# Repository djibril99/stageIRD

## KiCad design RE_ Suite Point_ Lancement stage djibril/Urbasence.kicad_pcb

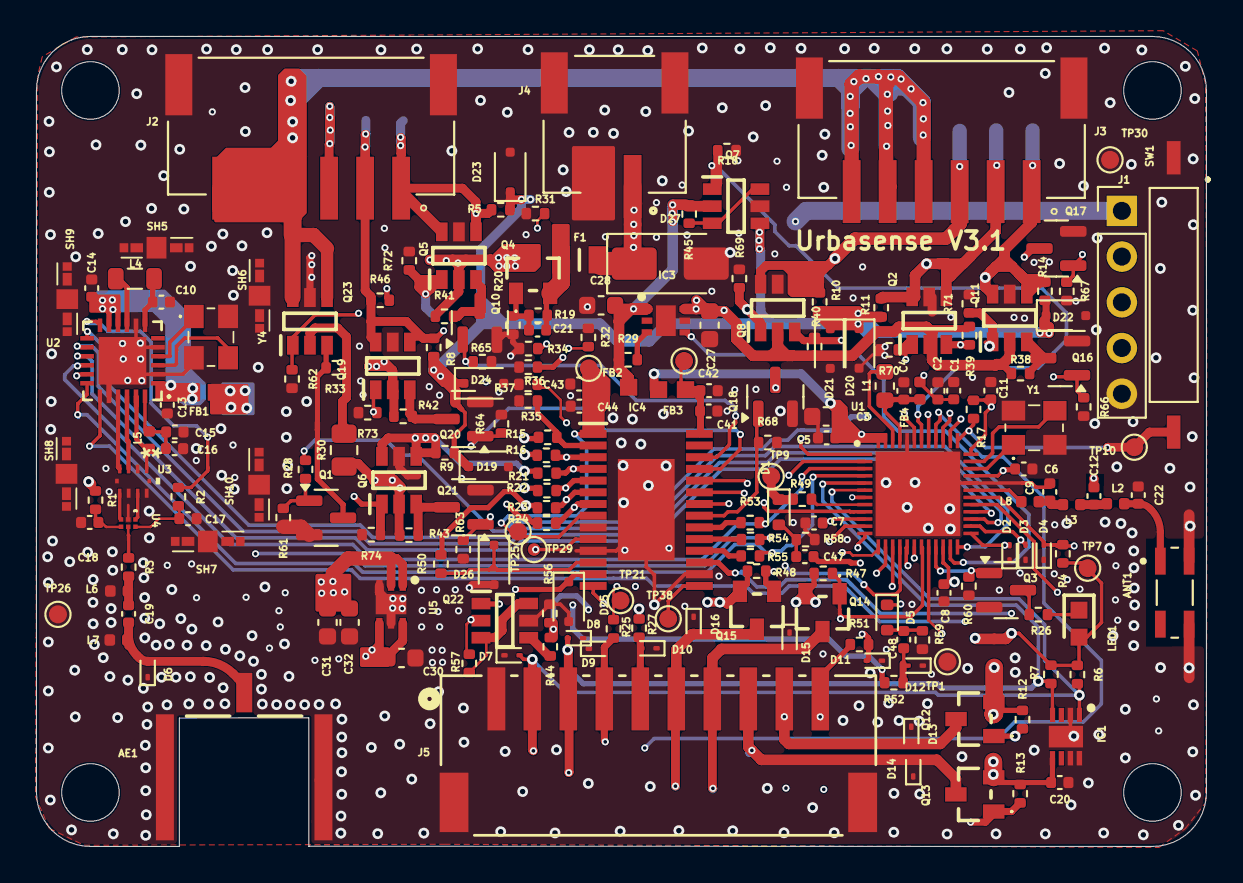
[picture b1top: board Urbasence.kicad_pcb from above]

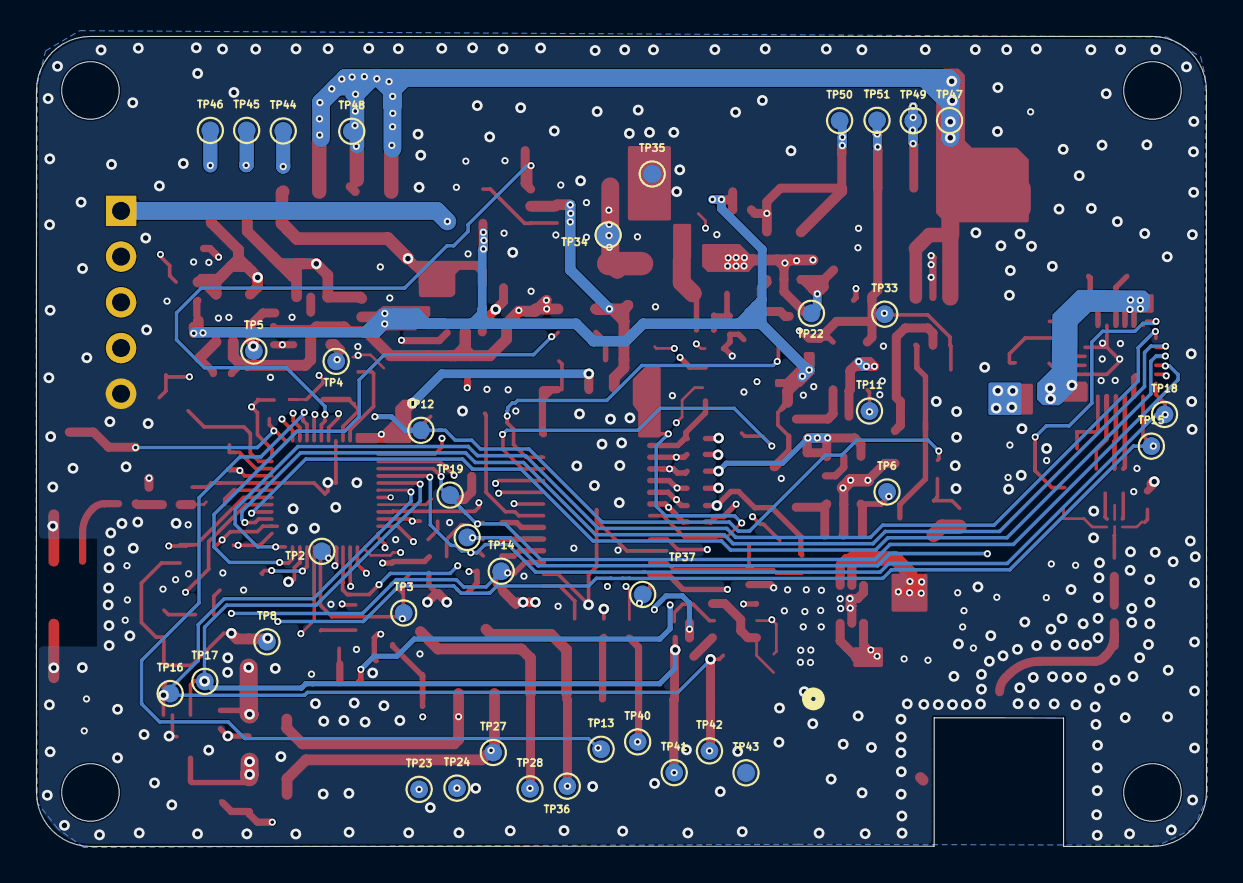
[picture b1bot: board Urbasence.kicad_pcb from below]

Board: 4 copper layers, 65.0 x 45.0 mm, 246 parts (38 on the bottom side), 124 nets.

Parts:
AE1: 60312202114307
ANT1: 2450AT42E0100E; XDCR_2450AT42E0100E
C1, C4, C41, C44: 2.2uF; C_0402_1005Metric
C2, C6: 10nF; C_0402_1005Metric
C3, C28, C31, C32: 10uF; C_0603_1608Metric
C5, C7, C8, C11, C14, C20, C42, C43: 100nF; C_0402_1005Metric
C9: 1.5pF; C_0402_1005Metric
C10: 470nF; C_0402_1005Metric
C12: 2pF; C_0402_1005Metric
C13, C21, C47, C48: 1uF; C_0402_1005Metric
C15: 47nF; C_0402_1005Metric
C16: 47pF; C_0402_1005Metric
C17, C18: 1nF; C_0402_1005Metric
C19: 4.7pF; C_0402_1005Metric
C22: 0.3pF; C_0402_1005Metric
C27: 1uF; C_0603_1608Metric
C30: 4.7uF/25V; C_0603_1608Metric
D1, D5: 1N4148WT; D_SOD-523
D2, D3, D4, D7, D8, D9, D10, D11, D12, D13, D14, D15, D16: ESD9B3.3ST5G; D_SOD-923
D6: ESD9B5.0ST5G; D_SOD-923
D19, D20, D21, D22, D23, D24, D25, D26: MM3Z5V1T1G; D_SOD-323F
D27: SMAJ9.0A; D_SMA
F1: MF-PSHT050KX-2; FUSE 500mA 0ZCK0050FF2E
FB1, FB2, FB3: 3A; FERIT_BLM18_0603_MUR
FB4: 3A; L_0402_1005Metric
H1, H2, H3, H4: MountingHole_Pad; MountingHole_3.2mm_M3
IC1: STS35-DIS; STS35-SON50P250X250X100-9N-D
IC3: TPS7A2650DRVR; TPS7A26-SON65P200X200X80-7N
IC4: LMP90100MHX_NOPB; LMP90100-SOP65P640X110-29N
J1: Flashing; PinHeader_1x05_P2.54mm_Vertical
J2, J3: Conn_01x06; JST_S6B-PH-SM4-TB_LF__SN_
J4: Conn_01x02; JST_S2B-PH-SM4-TB_LF__SN_
J5: Conn_01x10; CONN_S10B-PH-SM4-TBLFSN_JST
L1: 4.7uH; L_0603_1608Metric
L2, L3: 3.5nH; L_0402_1005Metric
L4: 15uH; L_0805_2012Metric
L5: 47nH; L_0402_1005Metric
L6, L7: 150nH; L_0402_1005Metric
L8: 2.7nH; L_0402_1005Metric
LED1: LED_0603
Q1, Q3, Q10, Q16, Q17, Q18, Q20, Q21: 2N7002; SOT-23
Q2, Q5, Q6, Q7, Q8, Q11, Q19, Q22, Q23: DMC2053-SOP95P280X100-6N
Q4, Q12, Q13, Q14, Q15: SSM3J372R,LF; SSM3J372RLF
R1, R2: 100R; R_0402_1005Metric
R3, R28, R49, R53, R54, R55: 0; R_0402_1005Metric
R4, R12, R13, R17, R18, R19, R29, R47, R48, R58, R59, R60, R61, R62, R63, R64, R65, R66, R67, R68, R69, R70, R71, R72, R73, R74: 10k; R_0402_1005Metric
R5, R8, R9, R10, R11, R14: 10k/0.5%; R_0402_1005Metric
R6, R7: 4.7k; R_0402_1005Metric
R15, R16, R21, R22, R23, R24: 1k/0.5%; R_0402_1005Metric
R20: 20k; R_0402_1005Metric
R25, R27: 22; R_0402_1005Metric
R26: 470R; R_0402_1005Metric
R30: 0; R_0805_2012Metric
R31, R32, R34, R35, R36, R37: 47k; R_0402_1005Metric
R33, R38, R39, R40, R41, R42, R43, R45: 100k; R_0402_1005Metric
R44: 27k; R_0402_1005Metric
R46, R50, R51, R52: 1k; R_0402_1005Metric
R56: 10K; R_0402_1005Metric
R57: 100K; R_0402_1005Metric
SH5, SH6, SH7, SH8, SH9, SH10: S0951-46R; S095146R
SW1: CT10-1530-G1
TP1, TP2, TP3, TP4, TP5, TP6, TP7, TP8, TP9, TP10, TP11, TP12, TP13, TP14, TP15, TP16, TP17, TP18, TP19, TP20, TP21, TP22, TP23, TP24, TP25, TP26, TP27, TP28, TP29, TP30, TP31, TP32, TP33, TP34, TP35, TP36, TP37, TP38, TP40, TP41, TP42, TP43, TP44, TP45, TP46, TP47, TP48, TP49, TP50, TP51: TestPoint; TestPoint_Pad_D1.0mm
U1: NRF54l15-QFAA; nRF52840-QFAA-F-R7
U2: SX1262IMLTRT
U3: 0900FM15K0039E; 0900FM15D0039E_JOT
U4: BGS12WN6E6327XTSA1; PG-TSNP-6-10_INF
U5: TLV76733DRVT; SON65P200X200X80-7N
Y1, Y4: 32MHz; ECS2501033BCKMTR

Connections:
3V3: C3.2, C5.2, C7.2, C8.2, C11.2, C20.2, C31.2, C32.2, FB1.2, FB3.1, IC1.5 (VDD), J1.1, LED1.2, Q12.2 (S), Q13.2 (S), Q14.2 (S), Q15.2 (S), R4.1, R6.1, R7.1, R12.1, R13.1, R17.1, R47.1, R48.1, TP7.1, TP8.1, U1.10 (VDD), U1.22 (VDD), U1.36 (VDD), U1.47 (Vdd), U1.48 (Vdd), U5.1 (OUT), U5.2 (SNS)
5V: C28.2, FB2.2, IC3.1 (OUT), Q7.2 (S2), R29.1, R45.1
/LMP90100/COM: J2.4, J2.5, J2.6, J3.4, J3.5, J3.6, Q23.4 (D2), Q23.6 (D2), TP47.1, TP48.1
/LMP90100/WM1/EV1: J2.1, Q5.4 (D2), Q5.6 (D2), R5.2, R15.1, R52.1, TP50.1
/LMP90100/WM2/EV2: J2.2, Q19.4 (D2), Q19.6 (D2), R8.2, R16.1, R46.1, TP51.1
/LMP90100/WM3/EV3: J2.3, Q6.4 (D2), Q6.6 (D2), R9.2, R21.1, TP49.1
/LMP90100/WM4/EV4: J3.1, Q11.4 (D2), Q11.6 (D2), R14.2, R22.1, TP46.1
/LMP90100/WM5/EV5: J3.2, Q2.4 (D2), Q2.6 (D2), R11.2, R23.1, R50.1, TP45.1
/LMP90100/WM6/EV6: J3.3, Q8.4 (D2), Q8.6 (D2), R10.2, R24.1, TP44.1
/nRF54L15/TOR/Counter1: D1.1 (K), R49.2, TP9.1
BAT_CHECK: IC4.10 (VIN6/VREFP2), R44.2, R56.1, TP29.1
BUSY: U1.27 (P0.02), U2.14 (BUSY)
CLK: R55.2, TP18.1, U1.4 (P1.03/NFC2), U2.18 (SCK)
CS1: TP15.1, U1.38 (P1.10), U2.19 (NSS)
CS2: IC4.17 (CSB), TP14.1, U1.39 (P1.11/AIN4/CK)
Control_COM: Q23.1 (G1), R62.1, TP33.1, U1.11 (P2.00)
Control_COM_Hi: R28.2, TP12.1, U1.41 (P1.13/AIN6)
Control_WM1: Q5.1 (G1), R72.1, TP22.1, U1.12 (P2.01/CK)
Control_WM1_Hi: IC4.26 (D5), Q10.1 (G), R65.1
Control_WM2: Q19.1 (G1), R73.1, TP11.1, U1.13 (P2.02)
Control_WM2_Hi: IC4.25 (D4), Q20.1 (G), R64.1
Control_WM3: Q6.1 (G1), R74.1, TP6.1, U1.14 (P2.03)
Control_WM3_Hi: IC4.24 (D3), Q21.1 (G), R63.1
Control_WM4: Q11.1 (G1), R71.1, TP5.1, U1.15 (P2.04)
Control_WM4_Hi: IC4.23 (D2), Q16.1 (G), R66.1
Control_WM5: Q2.1 (G1), R70.1, TP4.1, U1.16 (P2.05)
Control_WM5_Hi: IC4.22 (D1), Q17.1 (G), R67.1
Control_WM6: Q8.1 (G1), R69.1, U1.17 (P2.06/CK)
Control_WM6_Hi: IC4.21 (D0), Q18.1 (G), R68.1
Controled_5V: Q7.1 (G1), R18.1, U1.42 (P1.14/AIN7)
DIO1: U1.24 (P0.01), U2.13 (DIO1)
EN_5V: IC3.4 (EN), U1.23 (P0.00)
EN_BAT_CHECK: Q22.1 (G1), U1.9 (P1.08/EXTREF/CLK16M/ck)
ETX1: Q15.1 (G), R48.2, TP2.1, U1.18 (P2.07/SWO)
ETX2: Q14.1 (G), R47.2, TP3.1, U1.19 (P2.08)
ETX3: Q13.1 (G), R13.2, U1.20 (P2.09)
ETX4: Q12.1 (G), R12.2, U1.29 (P0.04CK)
GND: AE1.2, AE1.3, ANT1.3, ANT1.4, C1.1, C2.1, C3.1, C4.1, C5.1, C6.1, C7.1, C8.1, C9.1, C10.1, C11.1, C12.1, C13.1, C14.1, C15.2, C16.2, C17.2, C18.2, C20.1, C22.1, C27.1, C28.1, C30.1, C31.1, C32.1, C41.1, C42.1, C43.1, C44.1, D2.1 (A1), D3.1 (A1), D4.1 (A1), D6.1 (A1), D7.1 (A1), D8.1 (A1), D9.1 (A1), D10.1 (A1), D11.1 (A1), D12.1 (A1), D13.1 (A1), D14.1 (A1), D15.1 (A1), D16.1 (A1), D19.2 (A), D20.2 (A), D21.2 (A), D22.2 (A), D23.2 (A), D24.2 (A), D25.2 (A), D26.2 (A), D27.2 (A2), IC1.2 (ADDR), IC1.7 (R), IC1.8 (VSS), IC1.9 (GND), IC3.5 (GND), IC3.7 (EP), IC4.9 (VREFN1), IC4.11 (VIN7/VREFN2), IC4.16 (GND), IC4.29 (EP), J1.5, J2.S1, J2.S2, J3.S1, J3.S2, J4.2, J4.S2, J4.g, J5.1, J5.11, J5.12, L6.1, L7.1, Q1.2 (S), Q2.5 (S1), Q3.2 (S), Q5.5 (S1), Q6.5 (S1), Q7.5 (S1), Q8.5 (S1), Q10.2 (S), Q11.5 (S1), Q16.2 (S), Q17.2 (S), Q18.2 (S), Q19.5 (S1), Q20.2 (S), Q21.2 (S), Q22.5 (S1), Q23.5 (S1), R18.2, R20.2, R31.1, R32.1, R34.2, R35.1, R36.1, R37.1, R56.2, R58.2, R59.2, R60.2, R61.2, R62.2, R63.2, R64.2, R65.2, R66.2, R67.2, R68.2, R69.2, R70.2, R71.2, R72.2, R73.2, R74.2, SH5.1, SH5.2, SH5.3, SH5.4, SH5.5, SH6.1, SH6.2, SH6.3, SH6.4, SH6.5, SH7.1, SH7.2, SH7.3, SH7.4, SH7.5, SH8.1, SH8.2, SH8.3, SH8.4, SH8.5, SH9.1, SH9.2, SH9.3, SH9.4, SH9.5, SH10.1, SH10.2, SH10.3, SH10.4, SH10.5, SW1.1, TP1.1, TP26.1, TP30.1, TP35.1, TP43.1, U1.32 (Vss_PA), U1.44 (Vss), U1.49 (Vss), U2.2 (GND), U2.5 (GND), U2.8 (GND), U2.20 (GND), U2.25 (GND), U3.2 (GND), U3.5 (GND), U3.7 (GND), U3.9 (GND), U3.10 (GND), U4.2 (GND), U5.3 (GND_1), U5.5 (GND_2), U5.7 (EP), Y1.2, Y1.4, Y4.2, Y4.4
I2C_SCK: D8.2 (A2), IC1.4 (SCL), J5.3, R7.2, TP17.1, TP41.1, U1.5 (P1.04/AIN0)
I2C_SDA: D7.2 (A2), IC1.1 (SDA), J5.2, R6.2, TP16.1, TP42.1, U1.6 (P1.05/AIN1)
L_RESET: U1.28 (P0.03CK), U2.15 (NRESET)
MISO: R53.2, TP19.1, U1.3 (P1.02/NFC1), U2.16 (MISO)
MOSI: R54.2, TP20.1, U1.2 (P1.01/XL2), U2.17 (MOSI)
unnamed: ANT1.1, C22.2, L2.2
unnamed: C9.2, L3.1, L8.2
unnamed: C12.2, L2.1, L3.2
unnamed: C19.1, L6.2, R3.2
unnamed: C47.1, D1.2 (A), R58.1
unnamed: C48.1, D5.2 (A), R59.1
unnamed: AE1.1, C19.2, D6.2 (A2), L7.2
unnamed: D9.2 (A2), J5.4, R25.1, TP40.1
unnamed: D10.2 (A2), J5.5, R27.1
unnamed: C47.2, D11.2 (A2), R51.2
unnamed: C48.2, D12.2 (A2), R52.2
unnamed: D13.2 (A2), J5.9, Q12.3 (D), TP24.1
unnamed: D14.2 (A2), J5.8, Q13.3 (D), TP27.1
unnamed: D15.2 (A2), J5.7, Q14.3 (D), TP28.1
unnamed: D16.2 (A2), J5.6, Q15.3 (D), TP36.1
unnamed: D19.1 (K), D20.1 (K), D21.1 (K), D22.1 (K), D23.1 (K), D24.1 (K), Q7.4 (D2), R5.1, R8.1, R9.1, R10.1, R11.1, R14.1
unnamed: D25.1 (K), IC4.13 (IB1), R46.2
unnamed: D26.1 (K), IC4.12 (IB2), R50.2
unnamed: D27.1 (A1), F1.1, J4.1, TP34.1
unnamed: IC3.3 (PG), R29.2
unnamed: IC4.18 (SCLK), R55.1
unnamed: IC4.19 (SDI), R54.1
unnamed: IC4.20 (SDO/DRDYB), R53.1
unnamed: C43.2, C44.2, FB2.1, IC4.1 (VA), IC4.8 (VREFP1), TP25.1, TP32.1
unnamed: IC4.2 (VIN0), R15.2, R35.2
unnamed: IC4.3 (VIN1), R16.2, R37.2
unnamed: IC4.4 (VIN2), R21.2, R36.2
unnamed: IC4.5 (VIN3), R22.2, R34.1
unnamed: IC4.6 (VIN4), R23.2, R32.2
unnamed: IC4.7 (VIN5), R24.2, R31.2
unnamed: C41.2, C42.2, FB3.2, IC4.28 (VIO), TP31.1
unnamed: IC4.15 (XIN/CLK), TP38.1
unnamed: IC4.14 (XOUT), TP37.1
unnamed: J5.10, R51.1, TP23.1
unnamed: LED1.1, R26.1
unnamed: Q1.3 (D), Q23.3 (G2), R33.2
unnamed: Q1.1 (G), R28.1, R61.1
unnamed: Q3.3 (D), R26.2
unnamed: Q3.1 (G), R60.1, U1.21 (P2.10)
unnamed: C21.1, Q4.1 (G), R19.2, R20.1
unnamed: C21.2, F1.2, Q4.2 (S), R19.1
unnamed: Q7.3 (G2), Q7.6 (D2), R45.2
unnamed: Q5.3 (G2), Q10.3 (D), R41.2
unnamed: Q11.3 (G2), Q16.3 (D), R38.2
unnamed: Q2.3 (G2), Q17.3 (D), R39.2
unnamed: Q8.3 (G2), Q18.3 (D), R40.2
unnamed: Q19.3 (G2), Q20.3 (D), R42.2
unnamed: Q6.3 (G2), Q21.3 (D), R43.2
unnamed: Q22.3 (G2), Q22.6 (D2), R57.1
unnamed: Q22.4 (D2), R44.1
unnamed: Q23.2 (S2), R30.2, R33.1
unnamed: L8.1, U1.31 (Ant)
unnamed: L1.2, U1.46 (DCC)
unnamed: C1.2, C2.2, C6.2, FB4.2, U1.33 (DECRF), U1.43 (DECA)
unnamed: C4.2, FB4.1, L1.1, U1.45 (DECD)
unnamed: U1.34 (XC1), Y1.1
unnamed: U1.35 (XC2), Y1.3
unnamed: R49.1, U1.8 (P1.07/AIN3)
unnamed: R17.2, SW1.2, TP10.1, U1.37 (P1.09)
unnamed: L4.2, U2.9 (DCC_SW)
unnamed: R2.2, U2.12 (DIO2)
unnamed: U2.22 (RFI_N), U3.3 (RFI_N)
unnamed: U2.21 (RFI_P), U3.4 (RFI_P)
unnamed: L5.2, U2.23 (RFO), U3.1 (RFO)
unnamed: C10.2, L4.1, U2.7 (VREG)
unnamed: C15.1, C16.1, L5.1, U2.24 (VR_PA)
unnamed: U2.3 (XTA), Y4.3
unnamed: U2.4 (XTB), Y4.1
unnamed: U3.6 (SW_RFI), U4.3 (RF1)
unnamed: U3.8 (SW_RFO), U4.1 (RF2)
unnamed: C17.1, R2.1, U4.6 (CTRL)
unnamed: R3.1, U4.5 (RFIN)
unnamed: C18.1, R1.2, U4.4 (VDD)
RESET: D4.2 (A2), J1.4, R4.2, U1.30 (RESET)
RXD: R25.2, TP21.1, U1.1 (P1.00/XL1)
SWDCLK: D3.2 (A2), J1.3, U1.26 (SWDCLK)
SWDIO: D2.2 (A2), J1.2, U1.25 (SWDIO)
TOR/Counter2: D5.1 (K), U1.7 (P1.06/AIN2)
TXD: R27.2, TP13.1, U1.40 (P1.12/AIN5/CK)
V_RADIO: C13.2, C14.2, FB1.1, R1.1, U2.1 (VDD_IN), U2.10 (VBAT), U2.11 (VBAT_IO)
V_bat: C27.2, C30.2, IC3.6 (IN), Q2.2 (S2), Q4.3 (D), Q5.2 (S2), Q6.2 (S2), Q8.2 (S2), Q11.2 (S2), Q19.2 (S2), Q22.2 (S2), R30.1, R38.1, R39.1, R40.1, R41.1, R42.1, R43.1, R57.2, U5.4 (EN), U5.6 (IN)

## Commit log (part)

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2026-04-28 'first'
2026-04-28 first commits
2026-04-30 dernier
2026-05-04 derniere
2026-05-05 Ignore history folder

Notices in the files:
parts and their libraries:
Copyright 2021 Accelerated Designs. All rights reserved.
